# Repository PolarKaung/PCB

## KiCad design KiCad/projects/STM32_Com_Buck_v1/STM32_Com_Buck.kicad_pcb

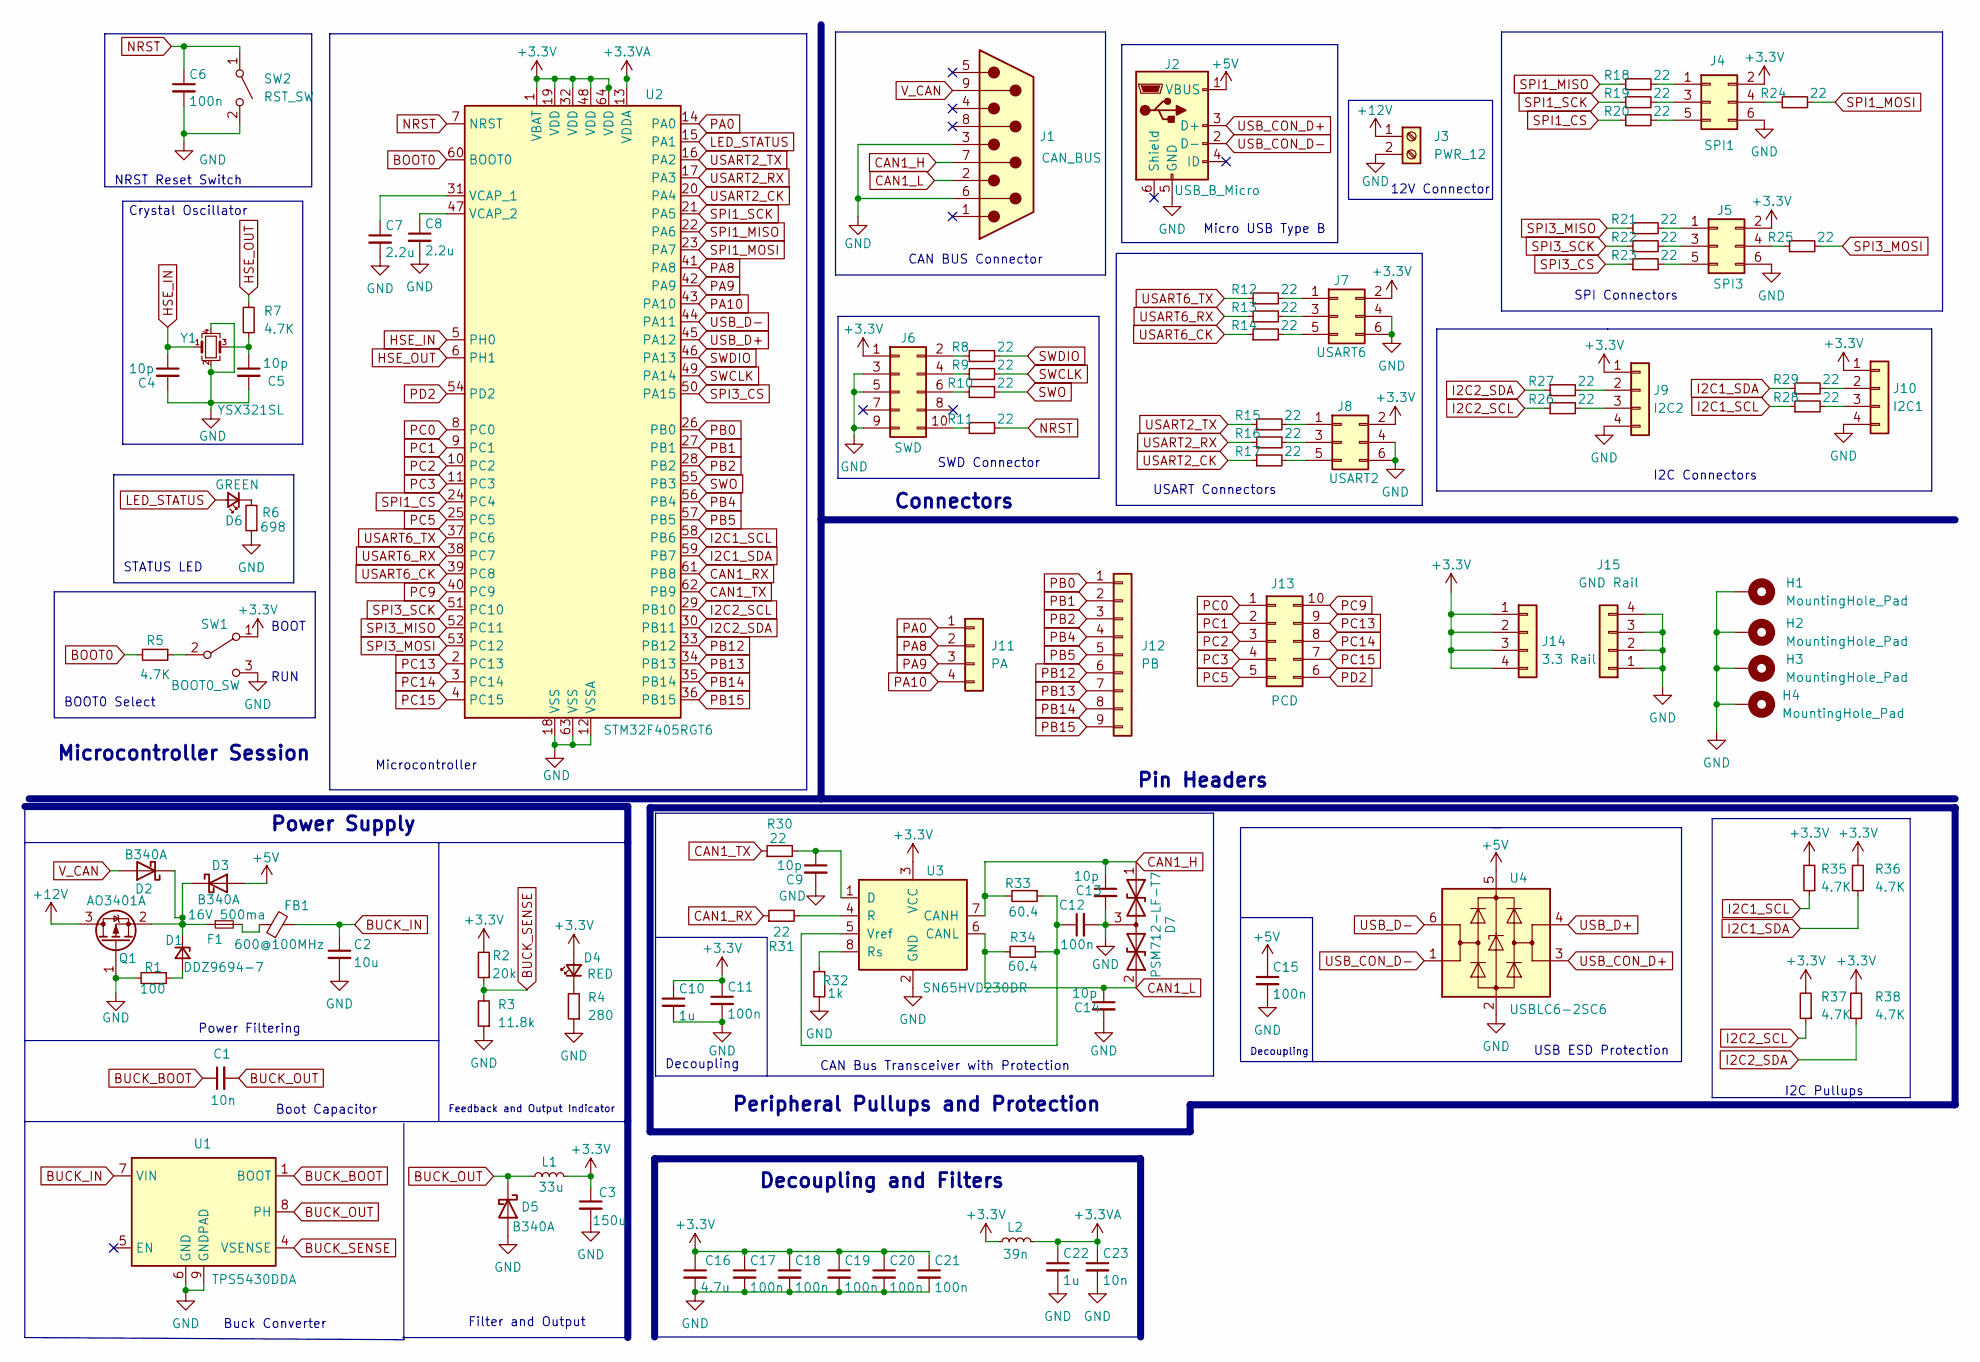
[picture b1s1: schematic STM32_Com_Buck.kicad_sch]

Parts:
C1, C23: 10n; C_0402_1005Metric
C2: 10u; C_0603_1608Metric
C3: 150u; CP_Elec_6.3x7.7
C4, C5, C9, C13, C14: 10p; C_0402_1005Metric
C6, C11, C12, C15, C17, C18, C19, C20, C21: 100n; C_0402_1005Metric
C7, C8: 2.2u; C_0402_1005Metric
C10: 1u; C_0402_1005Metric
C16: 4.7u; C_0603_1608Metric
C22: 1u; C_0603_1608Metric
D1: DDZ9694-7; D_SOD-123
D2, D3, D5: B340A; D_SMC
D4: RED; LED_0402_1005Metric
D6: GREEN; LED_0402_1005Metric
D7: PSM712-LF-T7; SOT-23
F1: 16V 500ma; Fuse_0603_1608Metric
FB1: 600@100MHz; L_0402_1005Metric
H1, H2, H3, H4: MountingHole_Pad; MountingHole_2.5mm_Pad_Via
J1: CAN_BUS; DSUB-9_Male_Horizontal_P2.77x2.84mm_EdgePinOffset7.70mm_Hou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
J2: USB_B_Micro; USB_Micro-B_Wuerth_629105150521
J3: PWR_12; TerminalBlock_Phoenix_PT-1,5-2-3.5-H_1x02_P3.50mm_Horizontal
J4: SPI1; PinHeader_2x03_P2.54mm_Vertical_SMD
J5: SPI3; PinHeader_2x03_P2.54mm_Vertical_SMD
J6: SWD; PinHeader_2x05_P2.54mm_Vertical_SMD
J7: USART6; PinHeader_2x03_P2.54mm_Vertical_SMD
J8: USART2; PinHeader_2x03_P2.54mm_Vertical_SMD
J9: I2C2; Molex_PicoBlade_53047-0410_1x04_P1.25mm_Vertical
J10: I2C1; Molex_PicoBlade_53047-0410_1x04_P1.25mm_Vertical
J11: PA; PinSocket_1x04_P1.00mm_Vertical
J12: PB; PinSocket_1x09_P1.00mm_Vertical
J13: PCD; PinSocket_2x05_P2.00mm_Vertical_SMD
J14: 3.3 Rail; PinSocket_1x04_P1.00mm_Vertical
J15: GND Rail; PinSocket_1x04_P1.00mm_Vertical
L1: 33u; L_7.1mm_6.6mm
L2: 39n; L_0402_1005Metric
Q1: AO3401A; SOT-23
R1: 100; R_0603_1608Metric
R2: 20k; R_0603_1608Metric
R3: 11.8k; R_0603_1608Metric
R4: 280; R_0603_1608Metric
R5, R7: 4.7K; R_0402_1005Metric
R6: 698; R_0603_1608Metric
R8, R9, R10, R11, R12, R13, R14, R15, R16, R17, R18, R19, R20, R21, R22, R23, R24, R25, R26, R27, R28, R29, R30, R31: 22; R_0402_1005Metric
R32: 1k; R_0402_1005Metric
R33, R34: 60.4; R_0603_1608Metric
R35, R36, R37, R38: 4.7K; R_0603_1608Metric
SW1: BOOT0_SW; SW_SPDT_PCM12
SW2: RST_SW; SW_Push_SPST_NO_Alps_SKRK
U1: TPS5430DDA; TI_SO-PowerPAD-8_ThermalVias
U2: STM32F405RGT6; LQFP-64_10x10mm_P0.5mm
U3: SN65HVD230DR; SOIC-8_3.9x4.9mm_P1.27mm
U4: USBLC6-2SC6; SOT-23-6
Y1: YSX321SL; Crystal_SMD_3225-4Pin_3.2x2.5mm

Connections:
+3.3VA: C22.1, C23.1, L2.2, U2.13 (VDDA)
+3V3: C3.1, C10.1, C11.1, C16.1, C17.1, C18.1, C19.1, C20.1, C21.1, D4.2 (A), J4.2, J5.2, J6.1, J7.2, J8.2, J9.1, J10.1, J14.1, J14.2, J14.3, J14.4, L1.2, L2.1, R2.2, R35.2, R36.2, R37.2, R38.2, SW1.1 (A), U2.1 (VBAT), U2.19 (VDD), U2.32 (VDD), U2.48 (VDD), U2.64 (VDD), U3.3 (VCC)
+5V: C15.1, D3.2 (A), J2.1 (VBUS), U4.5 (VBUS)
+12V: J3.1, Q1.3 (D)
BOOT0: R5.2, U2.60 (BOOT0)
BUCK_BOOT: C1.1, U1.1 (BOOT)
BUCK_IN: C2.1, FB1.2, U1.7 (VIN)
BUCK_OUT: C1.2, D5.1 (K), L1.1, U1.8 (PH)
BUCK_SENSE: R2.1, R3.2, U1.4 (VSENSE)
CAN1_H: C13.1, D7.1 (A1), J1.7, R33.2, U3.7 (CANH)
CAN1_L: C14.1, D7.2 (A2), J1.2, R34.2, U3.6 (CANL)
CAN1_RX: R31.1, U2.61 (PB8)
CAN1_TX: R30.1, U2.62 (PB9)
GND: C2.2, C3.2, C4.2, C5.2, C6.2, C7.2, C8.2, C9.2, C10.2, C11.2, C12.2, C13.2, C14.2, C15.2, C16.2, C17.2, C18.2, C19.2, C20.2, C21.2, C22.2, C23.2, D5.2 (A), D7.3 (common), H1.1, H2.1, H3.1, H4.1, J1.3, J1.6, J2.5 (GND), J3.2, J4.6, J5.6, J6.3, J6.5, J6.9, J7.4, J7.6, J8.4, J8.6, J9.4, J10.4, J15.1, J15.2, J15.3, J15.4, Q1.1 (G), R1.2, R3.1, R4.1, R6.1, R32.2, SW1.3 (C), SW2.2 (B), U1.6 (GND), U1.9 (GNDPAD), U2.12 (VSSA), U2.18 (VSS), U2.63 (VSS), U3.2 (GND), U4.2 (GND), Y1.2, Y1.4
HSE_IN: C4.1, U2.5 (PH0), Y1.1
HSE_OUT: R7.2, U2.6 (PH1)
I2C1_SCL: R28.1, R35.1, U2.58 (PB6)
I2C1_SDA: R29.1, R36.1, U2.59 (PB7)
I2C2_SCL: R26.1, R37.1, U2.29 (PB10)
I2C2_SDA: R27.1, R38.1, U2.30 (PB11)
LED_STATUS: D6.2 (A), U2.15 (PA1)
NRST: C6.1, R11.2, SW2.1 (A), U2.7 (NRST)
unnamed: C7.1, U2.31 (VCAP_1)
unnamed: C8.1, U2.47 (VCAP_2)
unnamed: D1.1 (K), D2.1 (K), D3.1 (K), F1.1, Q1.2 (S)
unnamed: F1.2, FB1.1
unnamed: J9.2, R27.2
unnamed: J9.3, R26.2
unnamed: J10.2, R29.2
unnamed: J10.3, R28.2
unnamed: D1.2 (A), R1.1
unnamed: D4.1 (K), R4.2
unnamed: R5.1, SW1.2 (B)
unnamed: D6.1 (K), R6.2
unnamed: C5.1, R7.1, Y1.3
unnamed: J6.2, R8.1
unnamed: J6.4, R9.1
unnamed: J6.6, R10.1
unnamed: J6.10, R11.1
unnamed: J7.1, R12.2
unnamed: J7.3, R13.2
unnamed: J7.5, R14.2
unnamed: J8.1, R15.2
unnamed: J8.3, R16.2
unnamed: J8.5, R17.2
unnamed: J4.1, R18.2
unnamed: J4.3, R19.2
unnamed: J4.5, R20.2
unnamed: J5.1, R21.2
unnamed: J5.3, R22.2
unnamed: J5.5, R23.2
unnamed: J4.4, R24.1
unnamed: J5.4, R25.1
unnamed: C9.1, R30.2, U3.1 (D)
unnamed: R31.2, U3.4 (R)
unnamed: R32.1, U3.8 (Rs)
unnamed: C12.1, R33.1, R34.1, U3.5 (Vref)
PA0: J11.1, U2.14 (PA0)
PA8: J11.2, U2.41 (PA8)
PA9: J11.3, U2.42 (PA9)
PA10: J11.4, U2.43 (PA10)
PB0: J12.1, U2.26 (PB0)
PB1: J12.2, U2.27 (PB1)
PB2: J12.3, U2.28 (PB2)
PB4: J12.4, U2.56 (PB4)
PB5: J12.5, U2.57 (PB5)
PB12: J12.6, U2.33 (PB12)
PB13: J12.7, U2.34 (PB13)
PB14: J12.8, U2.35 (PB14)
PB15: J12.9, U2.36 (PB15)
PC0: J13.1, U2.8 (PC0)
PC1: J13.2, U2.9 (PC1)
PC2: J13.3, U2.10 (PC2)
PC3: J13.4, U2.11 (PC3)
PC5: J13.5, U2.25 (PC5)
PC9: J13.10, U2.40 (PC9)
PC13: J13.9, U2.2 (PC13)
PC14: J13.8, U2.3 (PC14)
PC15: J13.7, U2.4 (PC15)
PD2: J13.6, U2.54 (PD2)
SPI1_CS: R20.1, U2.24 (PC4)
SPI1_MISO: R18.1, U2.22 (PA6)
SPI1_MOSI: R24.2, U2.23 (PA7)
SPI1_SCK: R19.1, U2.21 (PA5)
SPI3_CS: R23.1, U2.50 (PA15)
SPI3_MISO: R21.1, U2.52 (PC11)
SPI3_MOSI: R25.2, U2.53 (PC12)
SPI3_SCK: R22.1, U2.51 (PC10)
SWCLK: R9.2, U2.49 (PA14)
SWDIO: R8.2, U2.46 (PA13)
SWO: R10.2, U2.55 (PB3)
USART2_CK: R17.1, U2.20 (PA4)
USART2_RX: R16.1, U2.17 (PA3)
USART2_TX: R15.1, U2.16 (PA2)
USART6_CK: R14.1, U2.39 (PC8)
USART6_RX: R13.1, U2.38 (PC7)
USART6_TX: R12.1, U2.37 (PC6)
USB_CON_D+: J2.3 (D+), U4.3 (I/O2)
USB_CON_D-: J2.2 (D-), U4.1 (I/O1)
USB_D+: U2.45 (PA12), U4.4 (I/O2)
USB_D-: U2.44 (PA11), U4.6 (I/O1)
V_CAN: D2.2 (A), J1.9

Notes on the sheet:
Pin Headers
Microcontroller Session
Power Filtering
CAN BUS Connector
Power Supply
RUN
USB ESD Protection
Buck Converter
I2C Pullups
Crystal Oscillator
Decoupling
Filter and Output
Micro USB Type B
BOOT
SWD Connector
Connectors
12V Connector
STATUS LED
Decoupling and Filters
Feedback and Output Indicator
Boot Capacitor
BOOT0 Select
I2C Connectors
NRST Reset Switch
Peripheral Pullups and Protection
CAN Bus Transceiver with Protection
SPI Connectors
USART Connectors
Microcontroller

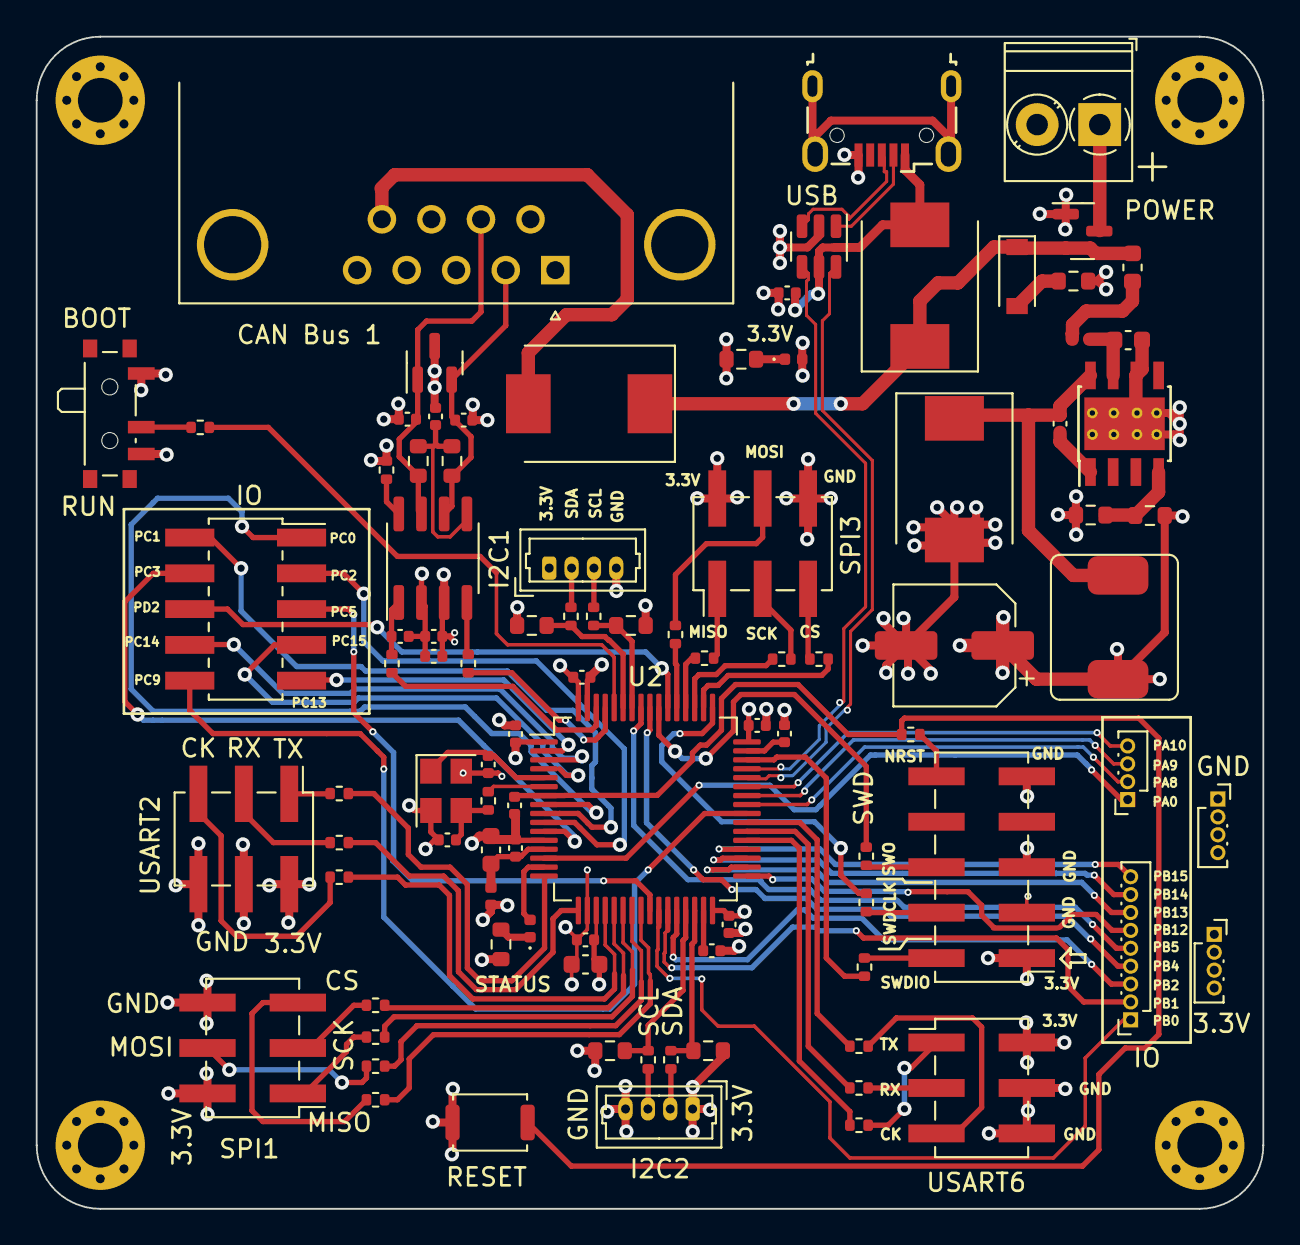
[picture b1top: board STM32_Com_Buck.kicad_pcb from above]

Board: 4 copper layers, 68.6 x 65.5 mm, 99 parts (0 on the bottom side), 102 nets.

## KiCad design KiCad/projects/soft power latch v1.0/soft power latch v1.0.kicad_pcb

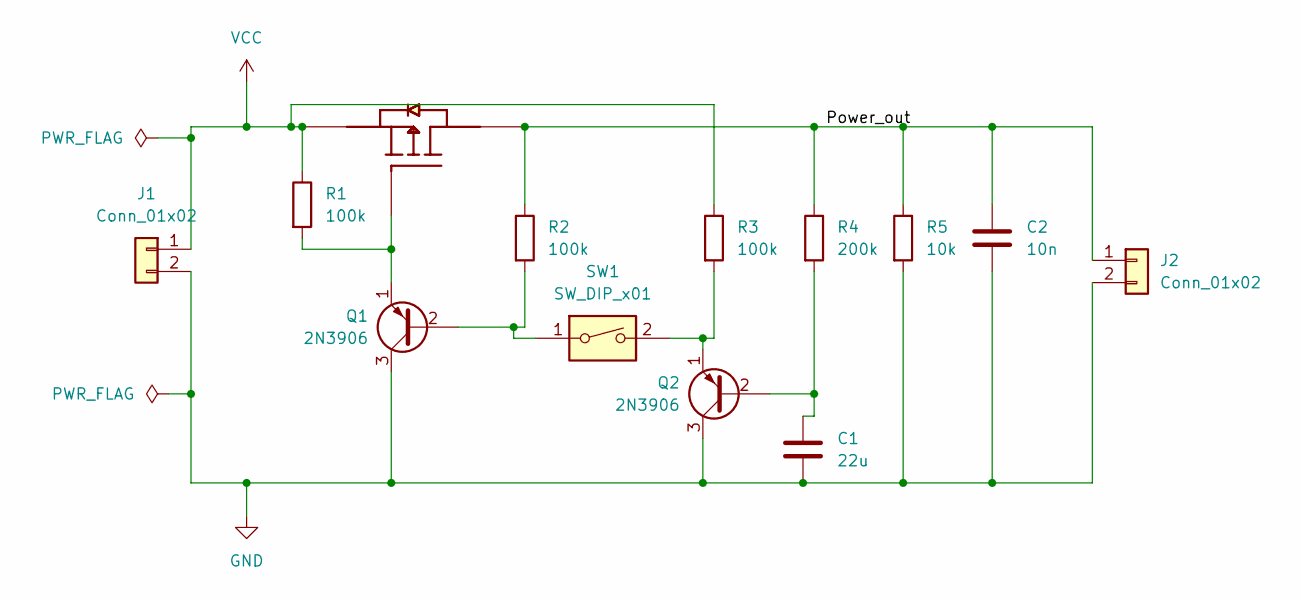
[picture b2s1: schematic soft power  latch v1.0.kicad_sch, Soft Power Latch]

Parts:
C1: 22u; CP_Radial_D10.0mm_P5.00mm
C2: 10n; C_Disc_D7.0mm_W2.5mm_P5.00mm
J1, J2: Conn_01x02; SolderWire-0.5sqmm_1x02_P4.8mm_D0.9mm_OD2.3mm
Q1, Q2: 2N3906; TO-92_Inline
Q3: IRF9640; TO254P1052X465X1989-3; PARTREV C
R1, R2, R3: 100k; R_Axial_DIN0414_L11.9mm_D4.5mm_P15.24mm_Horizontal
R4: 200k; R_Axial_DIN0414_L11.9mm_D4.5mm_P15.24mm_Horizontal
R5: 10k; R_Axial_DIN0414_L11.9mm_D4.5mm_P15.24mm_Horizontal
SW1: SW_DIP_x01; SW_CW_GPTS203211B

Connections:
/Power_out: C2.1, J2.1, Q3.2, R2.1, R4.1, R5.1
GND: C1.2, C2.2, J1.2, J2.2, Q1.3 (C), Q2.3 (C), R5.2
unnamed: C1.1, Q2.2 (B), R4.2
unnamed: Q1.1 (E), Q3.1, R1.2
unnamed: Q1.2 (B), R2.2, SW1.1
unnamed: Q2.1 (E), R3.2, SW1.2
VCC: J1.1, Q3.3, R1.1, R3.1

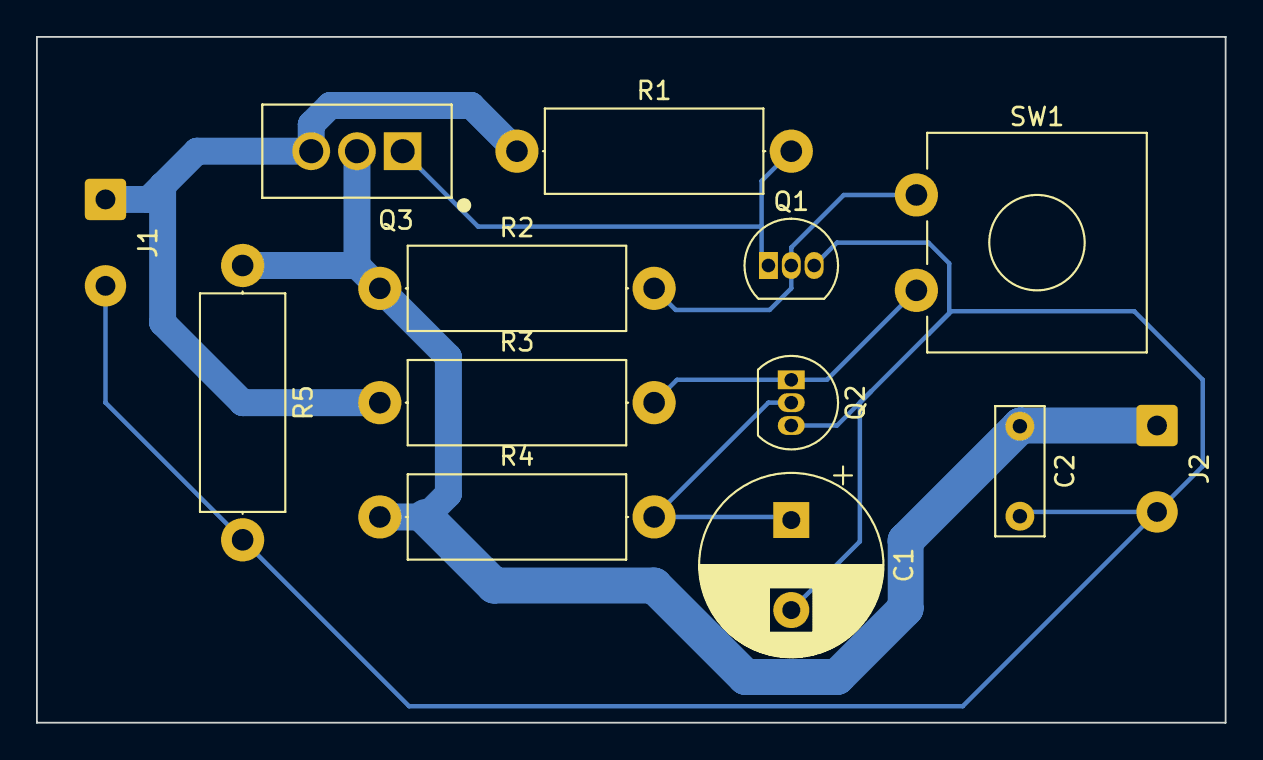
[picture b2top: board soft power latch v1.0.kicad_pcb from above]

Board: 2 copper layers, 66.0 x 38.1 mm, 13 parts (0 on the bottom side), 7 nets.

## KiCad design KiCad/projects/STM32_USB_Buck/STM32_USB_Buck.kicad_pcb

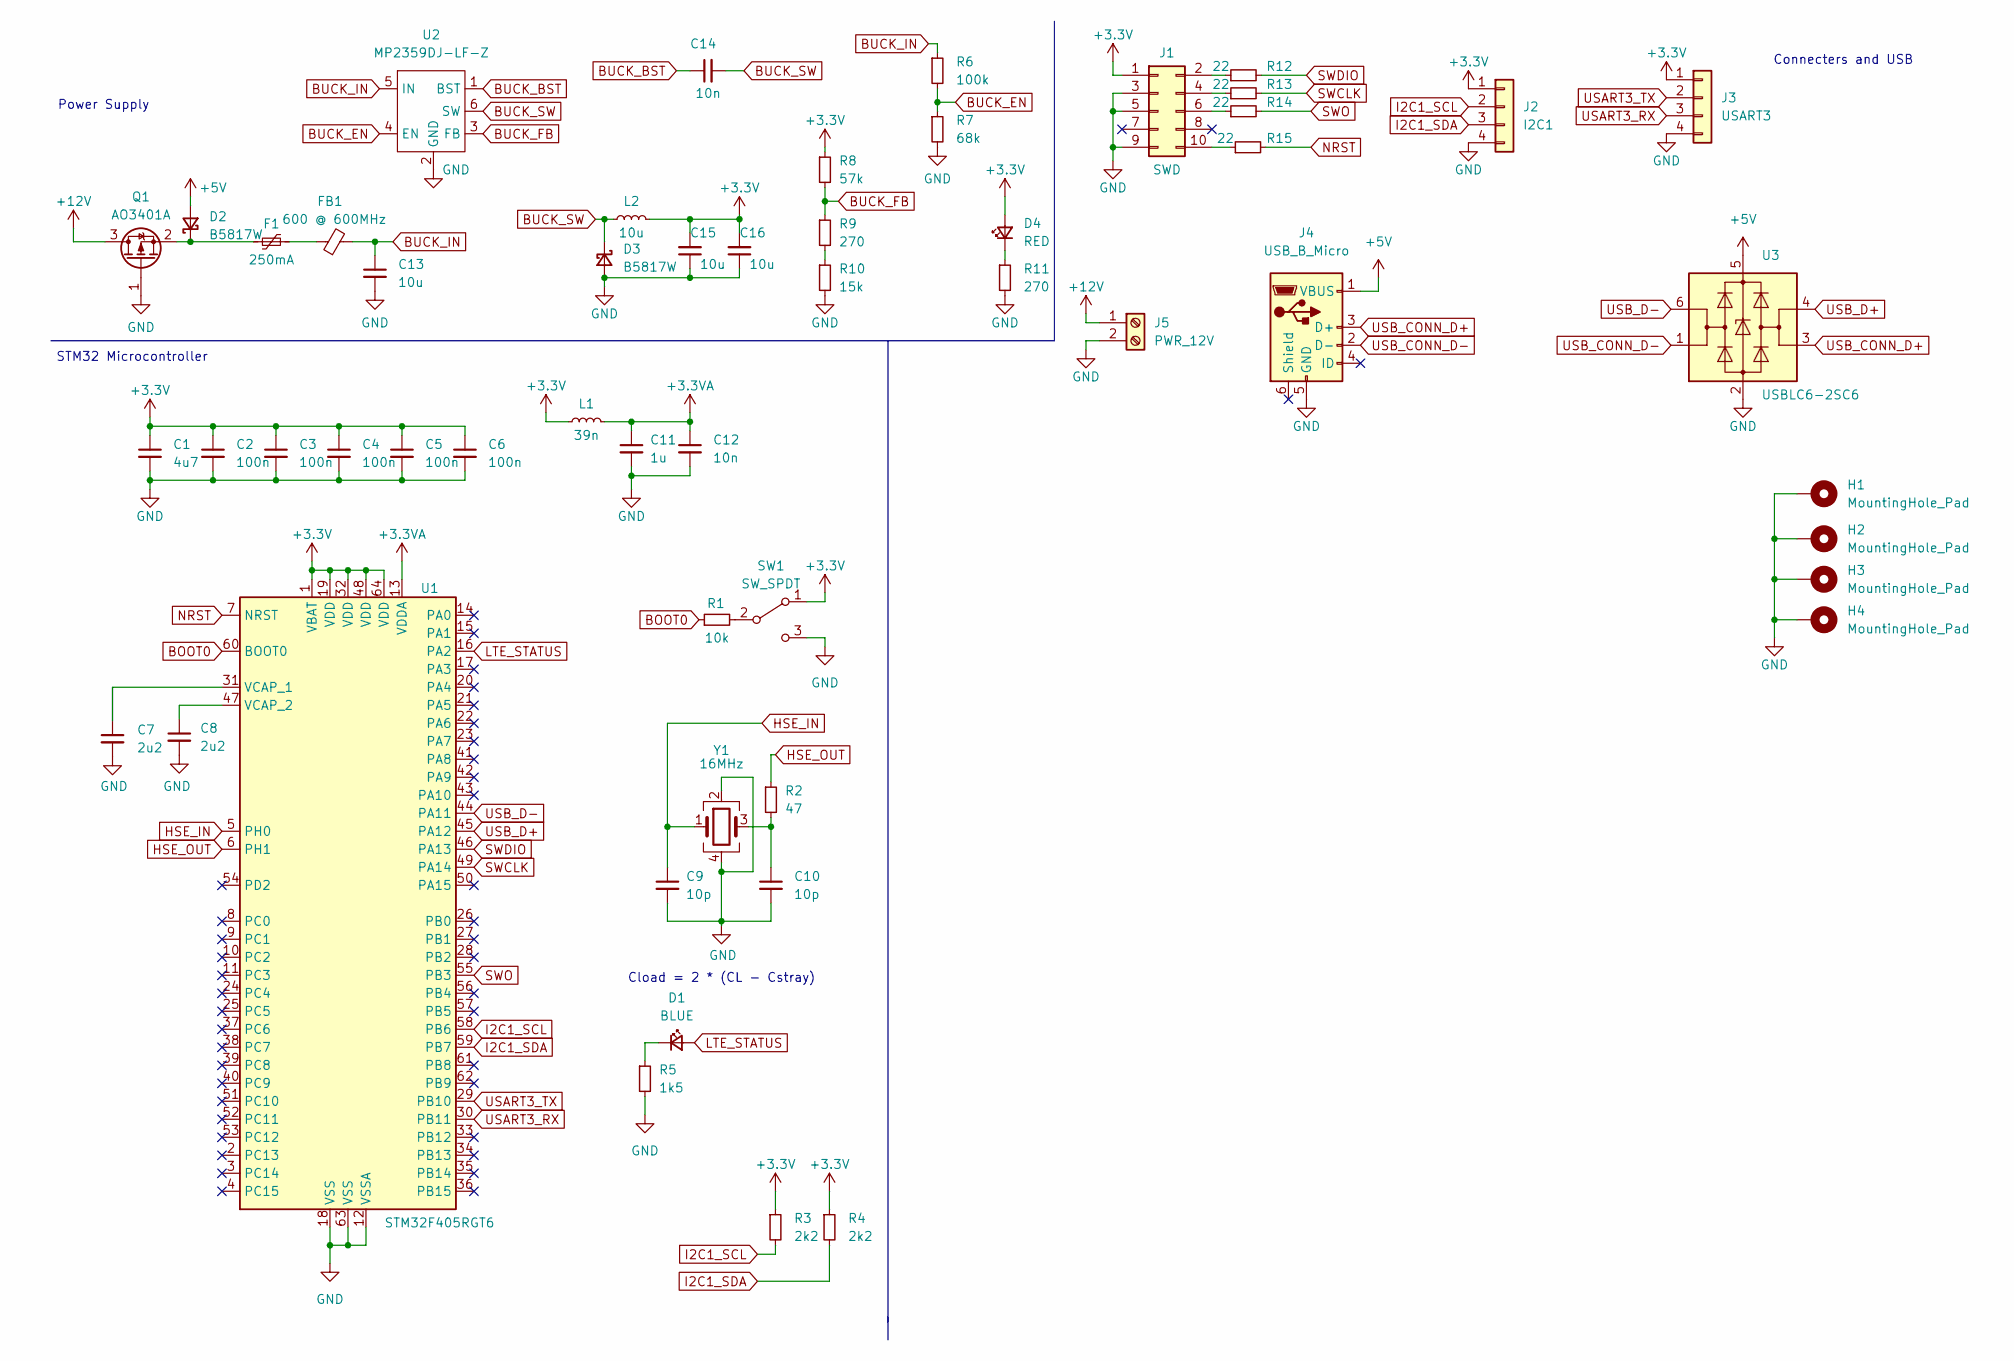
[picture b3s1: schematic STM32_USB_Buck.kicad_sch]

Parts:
C1: 4u7; C_0603_1608Metric; LCSC Part # C19666
C2, C3, C4, C5, C6: 100n; C_0402_1005Metric; LCSC Part # C307331
C7, C8: 2u2; C_0603_1608Metric; LCSC Part # C23630
C9, C10: 10p; C_0402_1005Metric; LCSC Part # C32949
C11: 1u; C_0402_1005Metric; LCSC Part # C52923
C12: 10n; C_0402_1005Metric; LCSC Part # C15195
C13, C15, C16: 10u; C_1206_3216Metric; LCSC Part # C13585
C14: 10n; C_0603_1608Metric; LCSC Part # C57112
D1: BLUE; LED_0603_1608Metric; LCSC Part # C72041
D2, D3: B5817W; D_SOD-123; LCSC Part # C8597
D4: RED; LED_0603_1608Metric; LCSC Part # C2286
F1: 250mA; Fuse_1206_3216Metric; LCSC Part # C135336
FB1: 600 @ 600MHz; L_0805_2012Metric; LCSC Part # C1017
H1, H2, H3, H4: MountingHole_Pad; MountingHole_4.3mm_M4_Pad_Via
J1: SWD; PinHeader_2x05_P1.27mm_Vertical_SMD
J2: I2C1; Molex_PicoBlade_53047-0410_1x04_P1.25mm_Vertical
J3: USART3; Molex_PicoBlade_53047-0410_1x04_P1.25mm_Vertical
J4: USB_B_Micro; USB_Micro-B_Wuerth_629105150521
J5: PWR_12V; TerminalBlock_Phoenix_PT-1,5-2-3.5-H_1x02_P3.50mm_Horizontal
L1: 39n; L_0402_1005Metric; LCSC Part # C335623
L2: 10u; L_Sunlord_MWSA0518_5.4x5.2mm; LCSC Part # C408412
Q1: AO3401A; SOT-23; LCSC Part # C15127
R1: 10k; R_0402_1005Metric; LCSC Part # C25744
R2: 47; R_0402_1005Metric; LCSC Part # C25792
R3, R4: 2k2; R_0201_0603Metric; LCSC Part # C166200
R5: 1k5; R_0603_1608Metric; LCSC Part # C22843
R6: 100k; R_0603_1608Metric; LCSC Part # C22936
R7: 68k; R_0603_1608Metric; LCSC Part # C23231
R8: 57k; R_0603_1608Metric; LCSC Part # C177435
R9, R11: 270; R_0603_1608Metric; LCSC Part # C22966
R10: 15k; R_0603_1608Metric; LCSC Part # C22809
R12, R13, R14, R15: 22; R_0402_1005Metric; LCSC Part # C25092
SW1: SW_SPDT; SW_SPDT_PCM12
U1: STM32F405RGT6; LQFP-64_10x10mm_P0.5mm; LCSC Part # C15742
U2: MP2359DJ-LF-Z; SOT-23-6; LCSC Part # C14259
U3: USBLC6-2SC6; SOT-23-6; LCSC Part # C2827654
Y1: 16MHz; Crystal_SMD_3225-4Pin_3.2x2.5mm; LCSC Part # C13738

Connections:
+3.3VA: C11.1, C12.1, L1.2, U1.13 (VDDA)
+3V3: C1.1, C2.1, C3.1, C4.1, C5.1, C6.1, C15.2, C16.2, D4.2 (A), J1.1, J2.1, J3.1, L1.1, L2.2, R3.1, R4.1, R8.1, SW1.1 (A), U1.1 (VBAT), U1.19 (VDD), U1.32 (VDD), U1.48 (VDD), U1.64 (VDD)
+5V: D2.2 (A), J4.1 (VBUS), U3.5 (VBUS)
+12V: J5.1, Q1.3 (D)
BOOT0: R1.1, U1.60 (BOOT0)
BUCK_BST: C14.1, U2.1 (BST)
BUCK_EN: R6.2, R7.1, U2.4 (EN)
BUCK_FB: R8.2, R9.1, U2.3 (FB)
BUCK_IN: C13.1, FB1.2, R6.1, U2.5 (IN)
BUCK_SW: C14.2, D3.1 (K), L2.1, U2.6 (SW)
GND: C1.2, C2.2, C3.2, C4.2, C5.2, C6.2, C7.2, C8.2, C9.2, C10.2, C11.2, C12.2, C13.2, C15.1, C16.1, D3.2 (A), H1.1, H2.1, H3.1, H4.1, J1.3, J1.5, J1.9, J2.4, J3.4, J4.5 (GND), J5.2, Q1.1 (G), R5.2, R7.2, R10.2, R11.2, SW1.3 (C), U1.12 (VSSA), U1.18 (VSS), U1.63 (VSS), U2.2 (GND), U3.2 (GND), Y1.2, Y1.4
HSE_IN: C9.1, U1.5 (PH0), Y1.1
HSE_OUT: R2.1, U1.6 (PH1)
I2C1_SCL: J2.2, R3.2, U1.58 (PB6)
I2C1_SDA: J2.3, R4.2, U1.59 (PB7)
LTE_STATUS: D1.2 (A), U1.16 (PA2)
NRST: R15.2, U1.7 (NRST)
unnamed: C7.1, U1.31 (VCAP_1)
unnamed: C8.1, U1.47 (VCAP_2)
unnamed: C10.1, R2.2, Y1.3
unnamed: D1.1 (K), R5.1
unnamed: D2.1 (K), F1.1, Q1.2 (S)
unnamed: D4.1 (K), R11.1
unnamed: F1.2, FB1.1
unnamed: J1.2, R12.1
unnamed: J1.4, R13.1
unnamed: J1.6, R14.1
unnamed: J1.10, R15.1
unnamed: R1.2, SW1.2 (B)
unnamed: R9.2, R10.1
SWCLK: R13.2, U1.49 (PA14)
SWDIO: R12.2, U1.46 (PA13)
SWO: R14.2, U1.55 (PB3)
USART3_RX: J3.3, U1.30 (PB11)
USART3_TX: J3.2, U1.29 (PB10)
USB_CONN_D+: J4.3 (D+), U3.3 (I/O2)
USB_CONN_D-: J4.2 (D-), U3.1 (I/O1)
USB_D+: U1.45 (PA12), U3.4 (I/O2)
USB_D-: U1.44 (PA11), U3.6 (I/O1)

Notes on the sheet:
Cload = 2 * (CL - Cstray)
Power Supply
STM32 Microcontroller
Connecters and USB

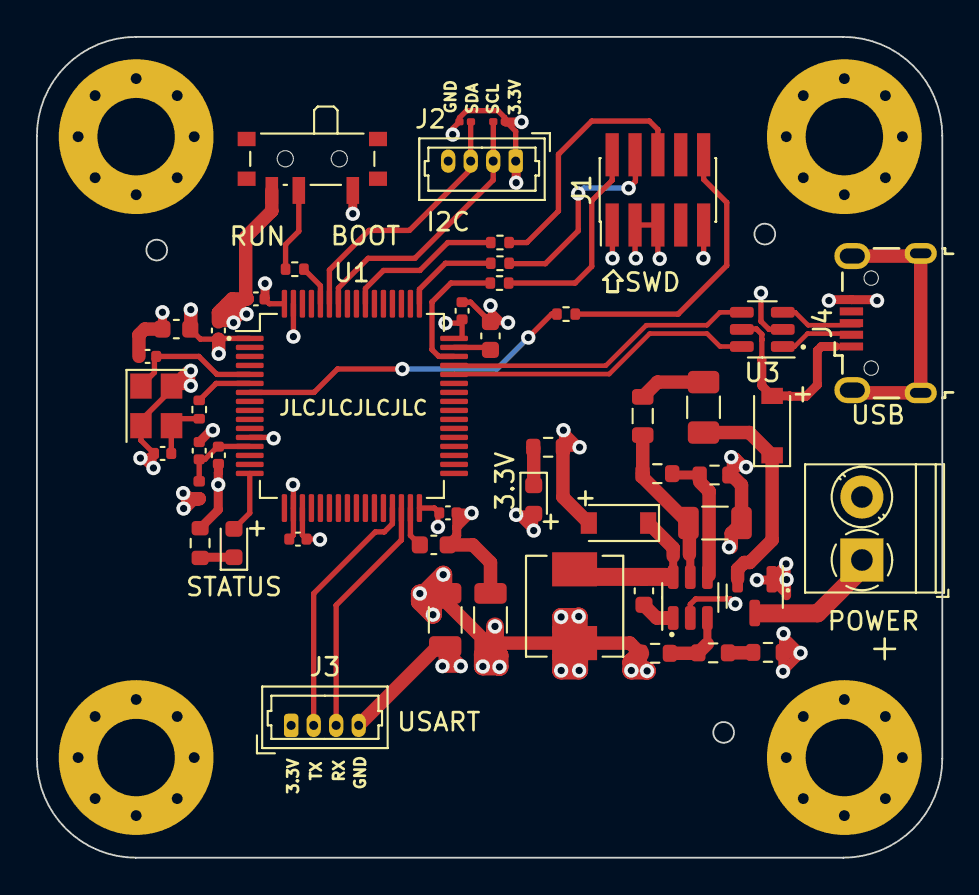
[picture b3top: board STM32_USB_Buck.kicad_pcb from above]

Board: 4 copper layers, 50.3 x 45.6 mm, 54 parts (0 on the bottom side), 39 nets.

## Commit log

2022-05-18 add kicad folder in kicad branch
2022-05-20 STM32_Com_Buck v_1
2022-05-20 added picture of STM32_Com_Buck_v1 Board
2022-05-20 added the schematic for stm32_com_buck_v1
